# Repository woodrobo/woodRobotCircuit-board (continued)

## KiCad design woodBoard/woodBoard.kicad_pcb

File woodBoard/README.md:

# woodBoard
ロボット回路のメインボード

趣味でロボコン的なロボットを動かす回路を作ろうプロジェクト（？）のメインボードである。  
PIC32MZを使用しており200MHz/330DMIPSらしい。（たぶん）  
woodBoardの特徴を説明すると  
- 通信ポートが豊富(アドレスが被っても安心設計)
    - CAN通信2ポート(各ポートに2つコネクタ搭載、終端抵抗ジャンパピンで設定可能)  
    - SPI通信2ポート(そのうち1つのポートはSS違いで4つコネクタ配置、もう1つはピンソケット)
    - I2C通信2ポート(そのうち1つのポートは4つコネクタ配置、もう1つはピンソケット)
    - UART5ポート(USBシリアルに1,通信ポートに2,ピンソケットに2)
- ほとんど秋月電子で部品購入可能
    - 一部は秋月電子で購入できないが
    - EHコネクタ->お好きなコネクタに変更
    - MCP2562->DIP品なら秋月電子で売っているのでピンソケットからCANTX,CANRXを取り出せば動作可能
    - 表面実装の24MHz水晶->スルーホール部品を"気合"または、違う周波数に変更する（ただしUSB通信をするには12MHzまたは24MHz）

# 部品について  
部品表.csvおよび部品個数表.csvを見てくれ。

# 基板ミス情報
- 「FT230XSの10番ピンである3V3OUT」-「GND」間に0.1uFのコンデンサを†気合い†で入れる必要がある。  
- 「NJM2391DL1-33」の出力側のコンデンサは積層セラミックコンデンサではなく電解コンデンサでなければならない。

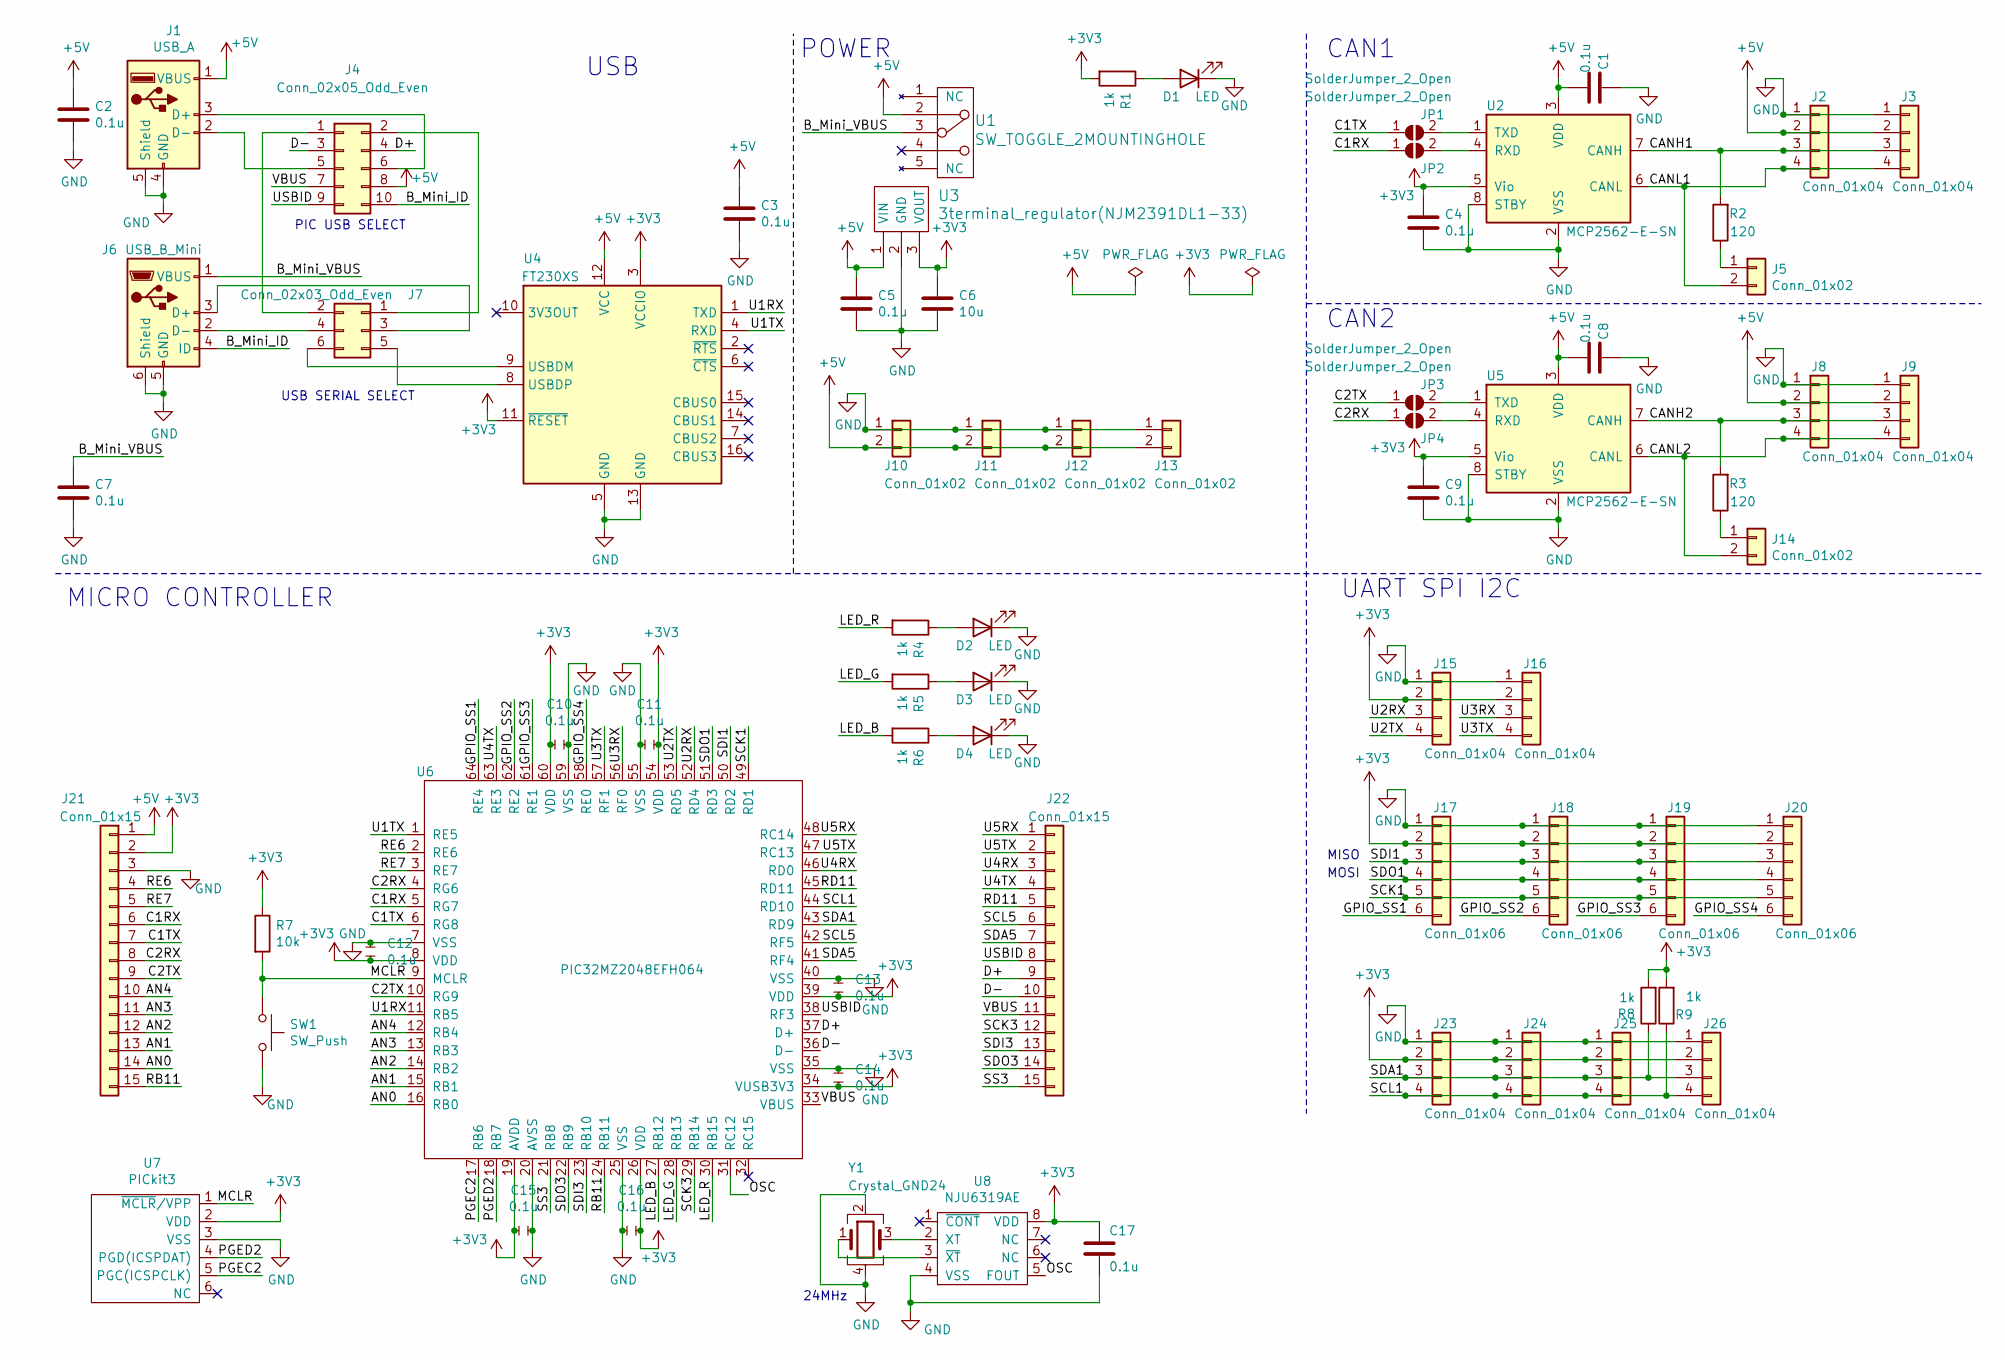
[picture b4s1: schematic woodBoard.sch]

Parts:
C1, C2, C3, C4, C5, C7, C8, C9, C10, C11, C12, C13, C14, C15, C16, C17: 0.1u; C_0603_1608Metric
C6: 10u; C_0603_1608Metric_Pad1.05x0.95mm_HandSolder
D1, D2, D3, D4: LED; LED_0603_1608Metric_Pad1.05x0.95mm_HandSolder
J1: USB_A; USB_A_Stewart_SS-52100-001_Horizontal
J2, J3, J8, J9, J15, J16, J23, J24, J25, J26: Conn_01x04; JST_EH_B4B-EH-A_1x04_P2.50mm_Vertical
J4: Conn_02x05_Odd_Even; PinHeader_2x05_P2.54mm_Vertical
J5, J14: Conn_01x02; PinHeader_1x02_P2.54mm_Vertical
J6: USB_B_Mini; USB_Mini-B_Wuerth_65100516121_Horizontal
J7: Conn_02x03_Odd_Even; PinHeader_2x03_P2.54mm_Vertical
J10, J11, J12, J13: Conn_01x02; JST_EH_B2B-EH-A_1x02_P2.50mm_Vertical
J17, J18, J19, J20: Conn_01x06; JST_EH_B6B-EH-A_1x06_P2.50mm_Vertical
J21, J22: Conn_01x15; PinSocket_1x15_P2.54mm_Vertical
JP1, JP2, JP3, JP4: SolderJumper_2_Open; SolderJumper-2_P1.3mm_Open_RoundedPad1.0x1.5mm
R1, R4, R5, R6, R8, R9: 1k; R_0603_1608Metric_Pad1.05x0.95mm_HandSolder
R2, R3: 120; R_0603_1608Metric_Pad1.05x0.95mm_HandSolder
R7: 10k; R_0603_1608Metric_Pad1.05x0.95mm_HandSolder
SW1: SW_Push; SW_TVAF06-A020B-R
U1: SW_TOGGLE_2MOUNTINGHOLE; SW_2MS1T1B4VS2QES
U2, U5: MCP2562-E-SN; SOIC-8_3.9x4.9mm_P1.27mm
U3: 3terminal_regulator(NJM2391DL1-33); TO-252-2
U4: FT230XS; QSOP-16_3.9x4.9mm_P0.635mm
U6: PIC32MZ2048EFH064; TQFP-64_10x10mm_P0.5mm
U7: PICkit3; PinHeader_1x06_P2.54mm_Vertical
U8: NJU6319AE; SO-8_3.9x4.9mm_P1.27mm
Y1: Crystal_GND24; Crystal_SMD_SeikoEpson_FA238V-4Pin_3.2x2.5mm_HandSoldering

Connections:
+3V3: C4.1, C6.1, C9.1, C10.1, C11.2, C12.2, C13.2, C14.2, C15.1, C16.2, C17.1, J15.2, J16.2, J17.2, J18.2, J19.2, J20.2, J21.2, J23.2, J24.2, J25.2, J26.2, R1.2, R7.1, R8.2, R9.2, U2.5 (Vio), U3.3 (VOUT), U4.3 (VCCIO), U4.11 (~RESET), U5.5 (Vio), U6.8 (VDD), U6.19 (AVDD), U6.26 (VDD), U6.34 (VUSB3V3), U6.39 (VDD), U6.54 (VDD), U6.60 (VDD), U7.2 (VDD), U8.8 (VDD)
+5V: C1.2, C2.1, C3.1, C5.1, C8.2, J1.1 (VBUS), J2.2, J3.2, J4.8, J8.2, J9.2, J10.2, J11.2, J12.2, J13.2, J21.1, U1.2, U2.3 (VDD), U3.1 (VIN), U4.12 (VCC), U5.3 (VDD)
/AN0: J21.14, U6.16 (RB0)
/AN1: J21.13, U6.15 (RB1)
/AN2: J21.12, U6.14 (RB2)
/AN3: J21.11, U6.13 (RB3)
/AN4: J21.10, U6.12 (RB4)
/B_Mini_ID: J4.10, J6.4 (ID)
/B_Mini_VBUS: C7.1, J6.1 (VBUS), U1.3
/C1RX: J21.6, JP2.1 (A), U6.5 (RG7)
/C1TX: J21.7, JP1.1 (A), U6.6 (RG8)
/C2RX: J21.8, JP4.1 (A), U6.4 (RG6)
/C2TX: J21.9, JP3.1 (A), U6.10 (RG9)
/CANH1: J2.3, J3.3, R2.2, U2.7 (CANH)
/CANH2: J8.3, J9.3, R3.2, U5.7 (CANH)
/CANL1: J2.4, J3.4, J5.2, U2.6 (CANL)
/CANL2: J8.4, J9.4, J14.2, U5.6 (CANL)
/D+: J4.4, J22.9, U6.37 (D+)
/D-: J4.3, J22.10, U6.36 (D-)
/GPIO_SS1: J17.6, U6.64 (RE4)
/GPIO_SS2: J18.6, U6.62 (RE2)
/GPIO_SS3: J19.6, U6.61 (RE1)
/GPIO_SS4: J20.6, U6.58 (RE0)
/LED_B: R6.2, U6.27 (RB12)
/LED_G: R5.2, U6.28 (RB13)
/LED_R: R4.2, U6.30 (RB15)
/MCLR: R7.2, SW1.1, U6.9 (MCLR), U7.1 (~MCLR~/VPP)
/OSC: U6.31 (RC12), U8.5 (FOUT)
/PGEC2: U6.17 (RB6), U7.5 (PGC(ICSPCLK))
/PGED2: U6.18 (RB7), U7.4 (PGD(ICSPDAT))
/RB11: J21.15, U6.24 (RB11)
/RD11: J22.5, U6.45 (RD11)
/RE6: J21.4, U6.2 (RE6)
/RE7: J21.5, U6.3 (RE7)
/SCK1: J17.5, J18.5, J19.5, J20.5, U6.49 (RD1)
/SCK3: J22.12, U6.29 (RB14)
/SCL1: J23.4, J24.4, J25.4, J26.4, R9.1, U6.44 (RD10)
/SCL5: J22.6, U6.42 (RF5)
/SDA1: J23.3, J24.3, J25.3, J26.3, R8.1, U6.43 (RD9)
/SDA5: J22.7, U6.41 (RF4)
/SDI1: J17.3, J18.3, J19.3, J20.3, U6.50 (RD2)
/SDI3: J22.13, U6.23 (RB10)
/SDO1: J17.4, J18.4, J19.4, J20.4, U6.51 (RD3)
/SDO3: J22.14, U6.22 (RB9)
/SS3: J22.15, U6.21 (RB8)
/U1RX: U4.1 (TXD), U6.11 (RB5)
/U1TX: U4.4 (RXD), U6.1 (RE5)
/U2RX: J15.3, U6.52 (RD4)
/U2TX: J15.4, U6.53 (RD5)
/U3RX: J16.3, U6.56 (RF0)
/U3TX: J16.4, U6.57 (RF1)
/U4RX: J22.3, U6.46 (RD0)
/U4TX: J22.4, U6.63 (RE3)
/U5RX: J22.1, U6.48 (RC14)
/U5TX: J22.2, U6.47 (RC13)
/USBID: J4.9, J22.8, U6.38 (RF3)
/VBUS: J4.7, J22.11, U6.33 (VBUS)
GND: C1.1, C2.2, C3.2, C4.2, C5.2, C6.2, C7.2, C8.1, C9.2, C10.2, C11.1, C12.1, C13.1, C14.1, C15.2, C16.1, C17.2, D1.1 (K), D2.1 (K), D3.1 (K), D4.1 (K), J1.4 (GND), J1.5 (Shield), J2.1, J3.1, J6.5 (GND), J6.6 (Shield), J8.1, J9.1, J10.1, J11.1, J12.1, J13.1, J15.1, J16.1, J17.1, J18.1, J19.1, J20.1, J21.3, J23.1, J24.1, J25.1, J26.1, SW1.2, U2.2 (VSS), U2.8 (STBY), U3.2 (GND), U4.5 (GND), U4.13 (GND), U5.2 (VSS), U5.8 (STBY), U6.7 (VSS), U6.20 (AVSS), U6.25 (VSS), U6.35 (VSS), U6.40 (VSS), U6.55 (VSS), U6.59 (VSS), U7.3 (VSS), U8.4 (VSS), Y1.2, Y1.4
unnamed: D1.2 (A), R1.1
unnamed: D2.2 (A), R4.1
unnamed: D3.2 (A), R5.1
unnamed: D4.2 (A), R6.1
unnamed: J1.2 (D-), J4.5
unnamed: J1.3 (D+), J4.6
unnamed: J4.1, J7.2
unnamed: J4.2, J7.1
unnamed: J5.1, R2.1
unnamed: J6.2 (D-), J7.4
unnamed: J6.3 (D+), J7.3
unnamed: J7.5, U4.8 (USBDP)
unnamed: J7.6, U4.9 (USBDM)
unnamed: J14.1, R3.1
unnamed: JP1.2 (B), U2.1 (TXD)
unnamed: JP2.2 (B), U2.4 (RXD)
unnamed: JP3.2 (B), U5.1 (TXD)
unnamed: JP4.2 (B), U5.4 (RXD)
unnamed: U8.2 (XT), Y1.3
unnamed: U8.3 (~XT), Y1.1

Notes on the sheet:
CAN1
MICRO CONTROLLER
PIC USB SELECT
USB SERIAL SELECT
UART SPI I2C
CAN2
MISO
MOSI
POWER
USB
24MHz

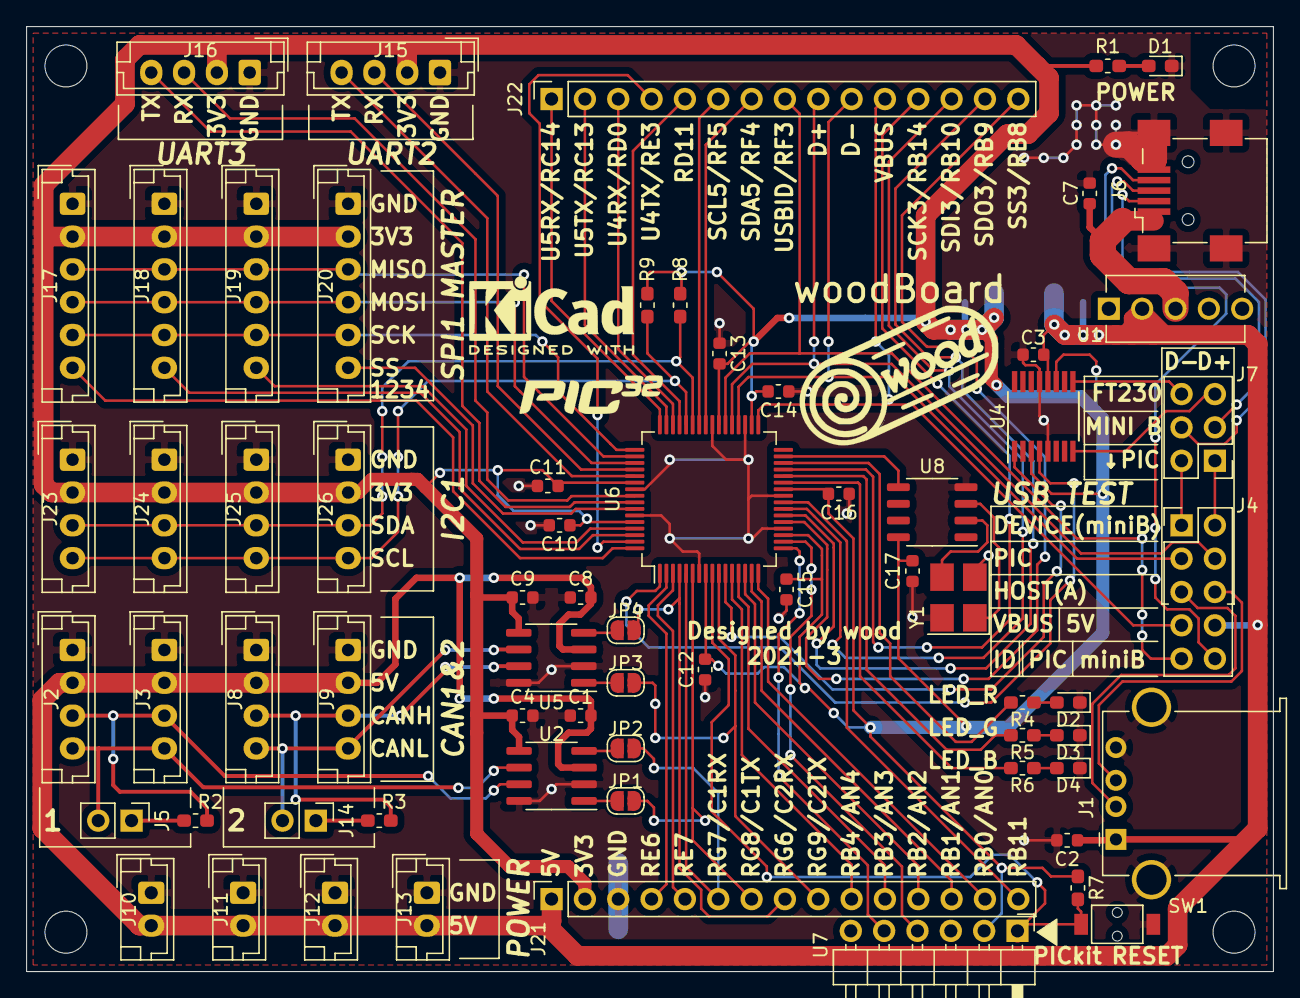
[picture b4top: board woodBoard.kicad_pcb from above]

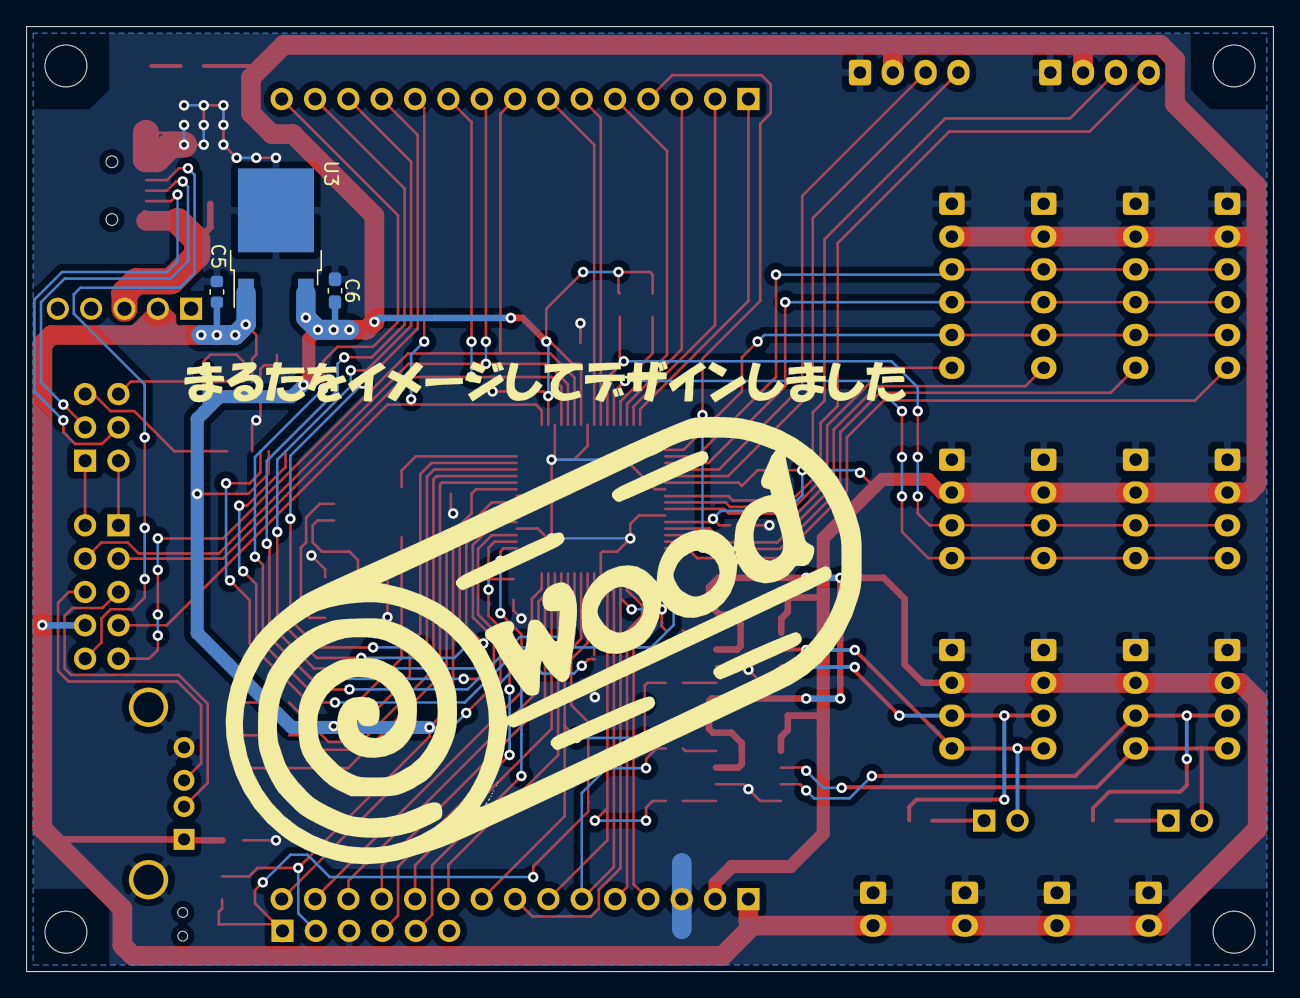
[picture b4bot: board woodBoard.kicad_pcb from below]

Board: 2 copper layers, 95.0 x 72.0 mm, 70 parts (3 on the bottom side), 78 nets.

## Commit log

2021-03-28 とりあえず基板完成のやつ
2021-03-28 部品表、部品個数表追加
2021-03-28 部品表ちょっと修正
2021-03-28 READMEにいろいろ書いた
2021-03-28 フォルダ構造変えた
2022-08-18 リポジトリの構造を複数のプロジェクトを入れれるようにした
2022-08-18 電流制御モタドラwoodCurrentMD無印と2を追加した
2022-08-18 woodTerminal追加
2022-08-23 全体の説明
2022-08-23 woodBoardのkicad_wood_libがsubmoduleになってないのを直した
2022-08-27 雑にwoodCurrentMD2とwoodTerminalのreadme書いた、後で修正
2022-08-27 woodCurrentMDのreadmeを微小量かいた
2022-08-29 woodCurrentMD2の価格書いた
2022-08-31 woodCurrentMD2のreadmeを修正
2022-09-05 woodBoardのミス説明とboothのURLを追加
2022-09-05 ファームウェアのリポジトリを一時的にkanojo_roboブランチに飛ばすようにした(こっちのほうが最新なので)
2022-09-22 woodTerminalの説明追加
2022-09-23 woodTerminalとwoodCurrentMD2のreadmeを修正
2022-09-23 woodTerminalの画像のリンク直し
